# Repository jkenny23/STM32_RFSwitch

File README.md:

# STM32_RFSwitch
12V RF switch/DC relay controller (7 channels) and open-drain button press emulator (6 channels) with switchable USB2.0/USB3.0 ports with independent voltage/current monitoring. Includes 2 thermistor channels, and 2 spare ADC, 2 spare GPIO, and 1 spare GPI channel.

Zip file contains Gerbers ready for fab (2-up panel), and xlsx files contain BOM/component placement list also needed for fab by JLCPCB SMT service. Estimated cost is $61.77 for PCBA including DHL shipping (10 boards total, 5 panels), plus $18.12 for additional components from LCSC (through hole headers, inductor, USB connectors), and $16.86 for the STM32 "blue pill" microcontroller boards, for a total of $96.75 ($9.68 per board).

Usage:

RF Switch: r[1-7]

USB2.0 Power Control: l[1-2, 1=off, 2=on]

USB3.0 Power Control:  m[1-2, 1=off, 2=on]

Open Drain Output: o[1-6] l[level: 0 = open, 1 = low, default 0] d[delay, x0.1s, deafult 10 (1s)]

Cal R/W Mode: t[r/w] a[address: 0-999] d[data, unsigned int (0-65535)]

Version: v

Status: s

Soft Reset: z

Help (Prints this menu): ?

# Compatible RF Switches

| RF Switch P/N | RF Switch Mfg. | RF Switch Config | # IOs | CH/CL | Notes                                                             | RF Switch Datasheet                                                                        | Approx. Price         |
|---------------|----------------|------------------|-------|-------|-------------------------------------------------------------------|--------------------------------------------------------------------------------------------|-----------------------|
| 2SE1T11JB     | Ducommun       | SPDT             | 2     | CL    |                                                                   | https://www.ducommun.com/pdf/mwcat/2s.pdf                                                  | $18.75-20             |
| 431-420823    | Dow-Key        | SP3T             | 3     | CH    | Remove pull up resistor (R5/R15/R19/R25/R38/R47/R55) for IOs used | https://www.dowkey.com/wp-content/uploads/2015/06/_plk49_1_431461_Latching_CatalogPage.pdf | ~$36 (similar models) |

# Errata
The +/- input are swapped for the MCP6002 op-amp 2 (USB3.0 current measurement). The traces need to be cut and jumpered per the image below:

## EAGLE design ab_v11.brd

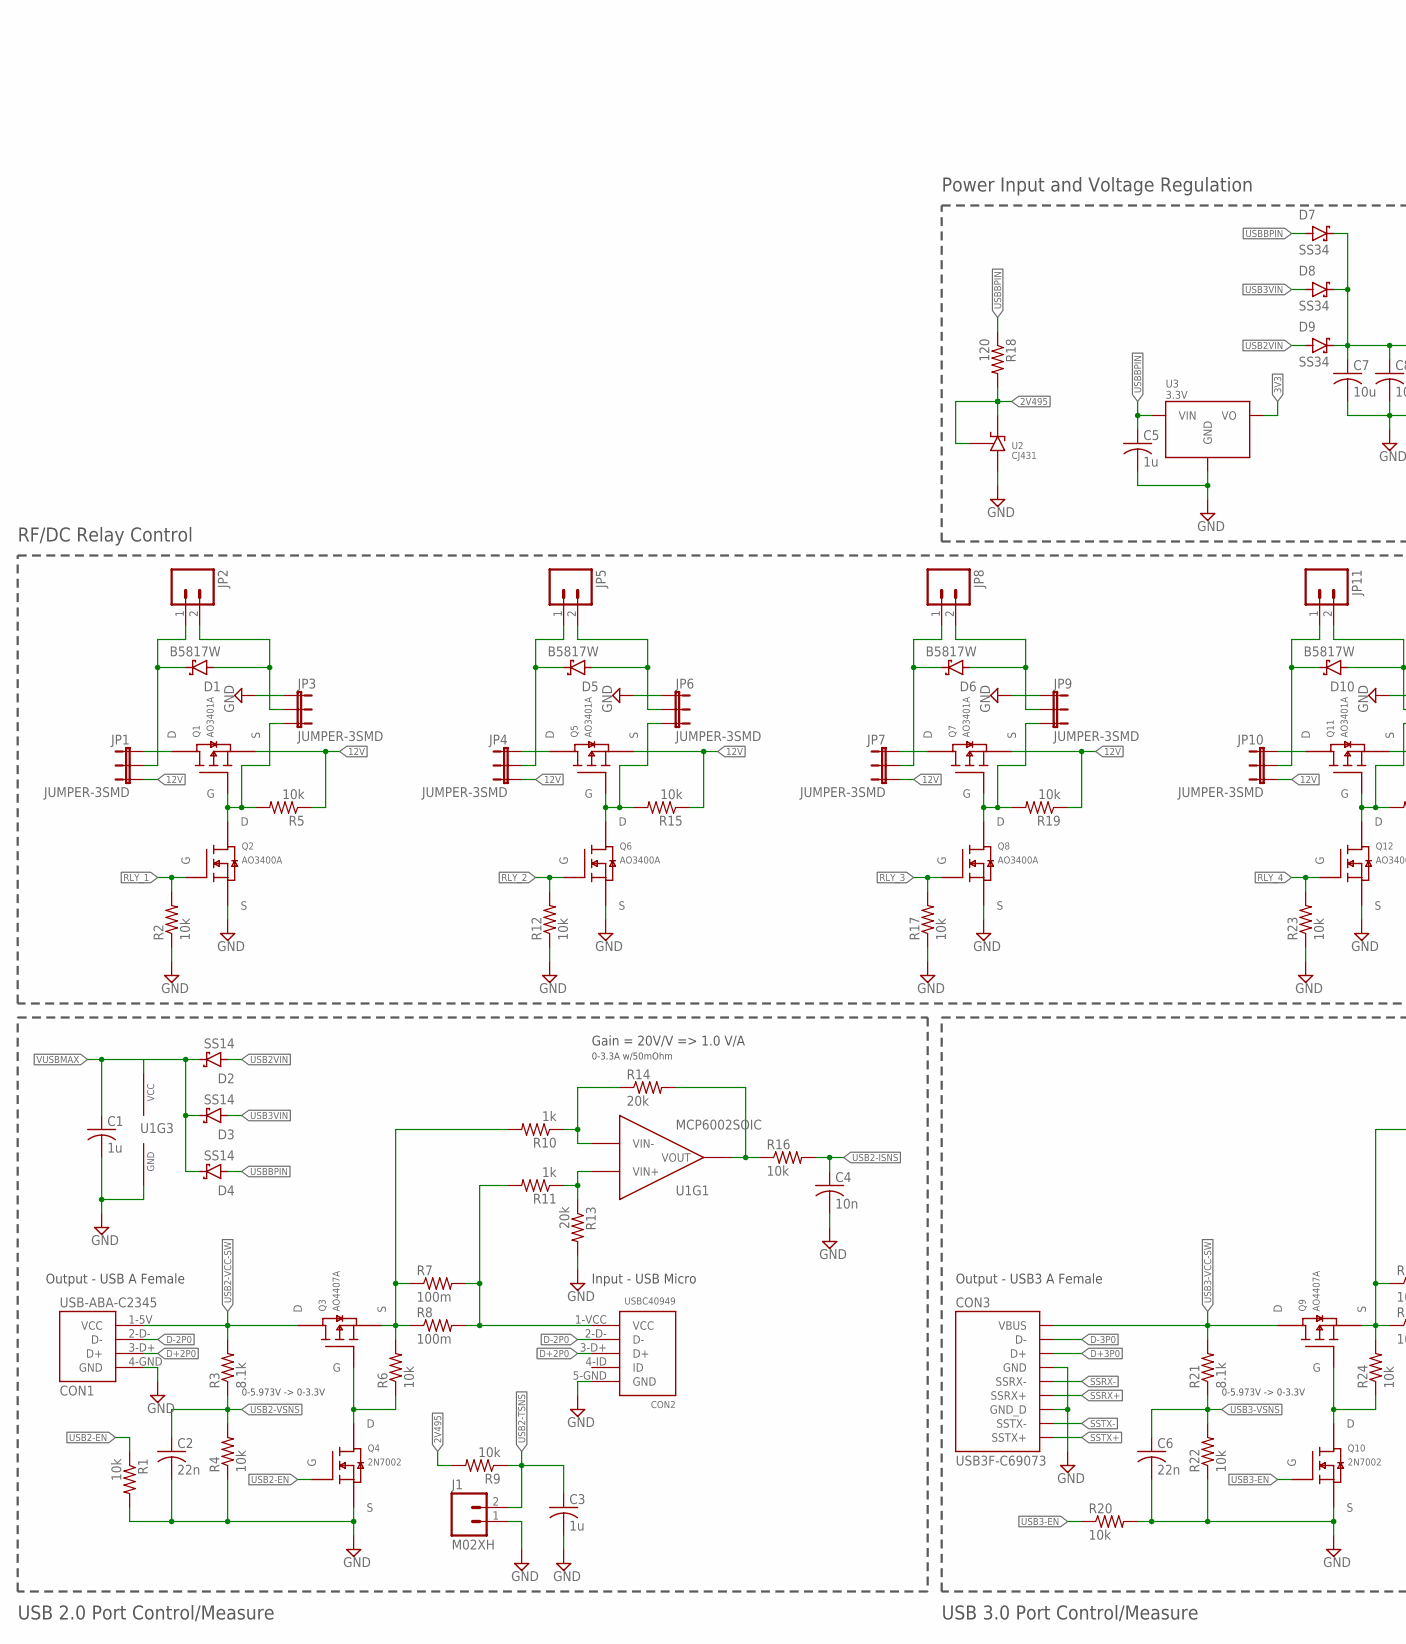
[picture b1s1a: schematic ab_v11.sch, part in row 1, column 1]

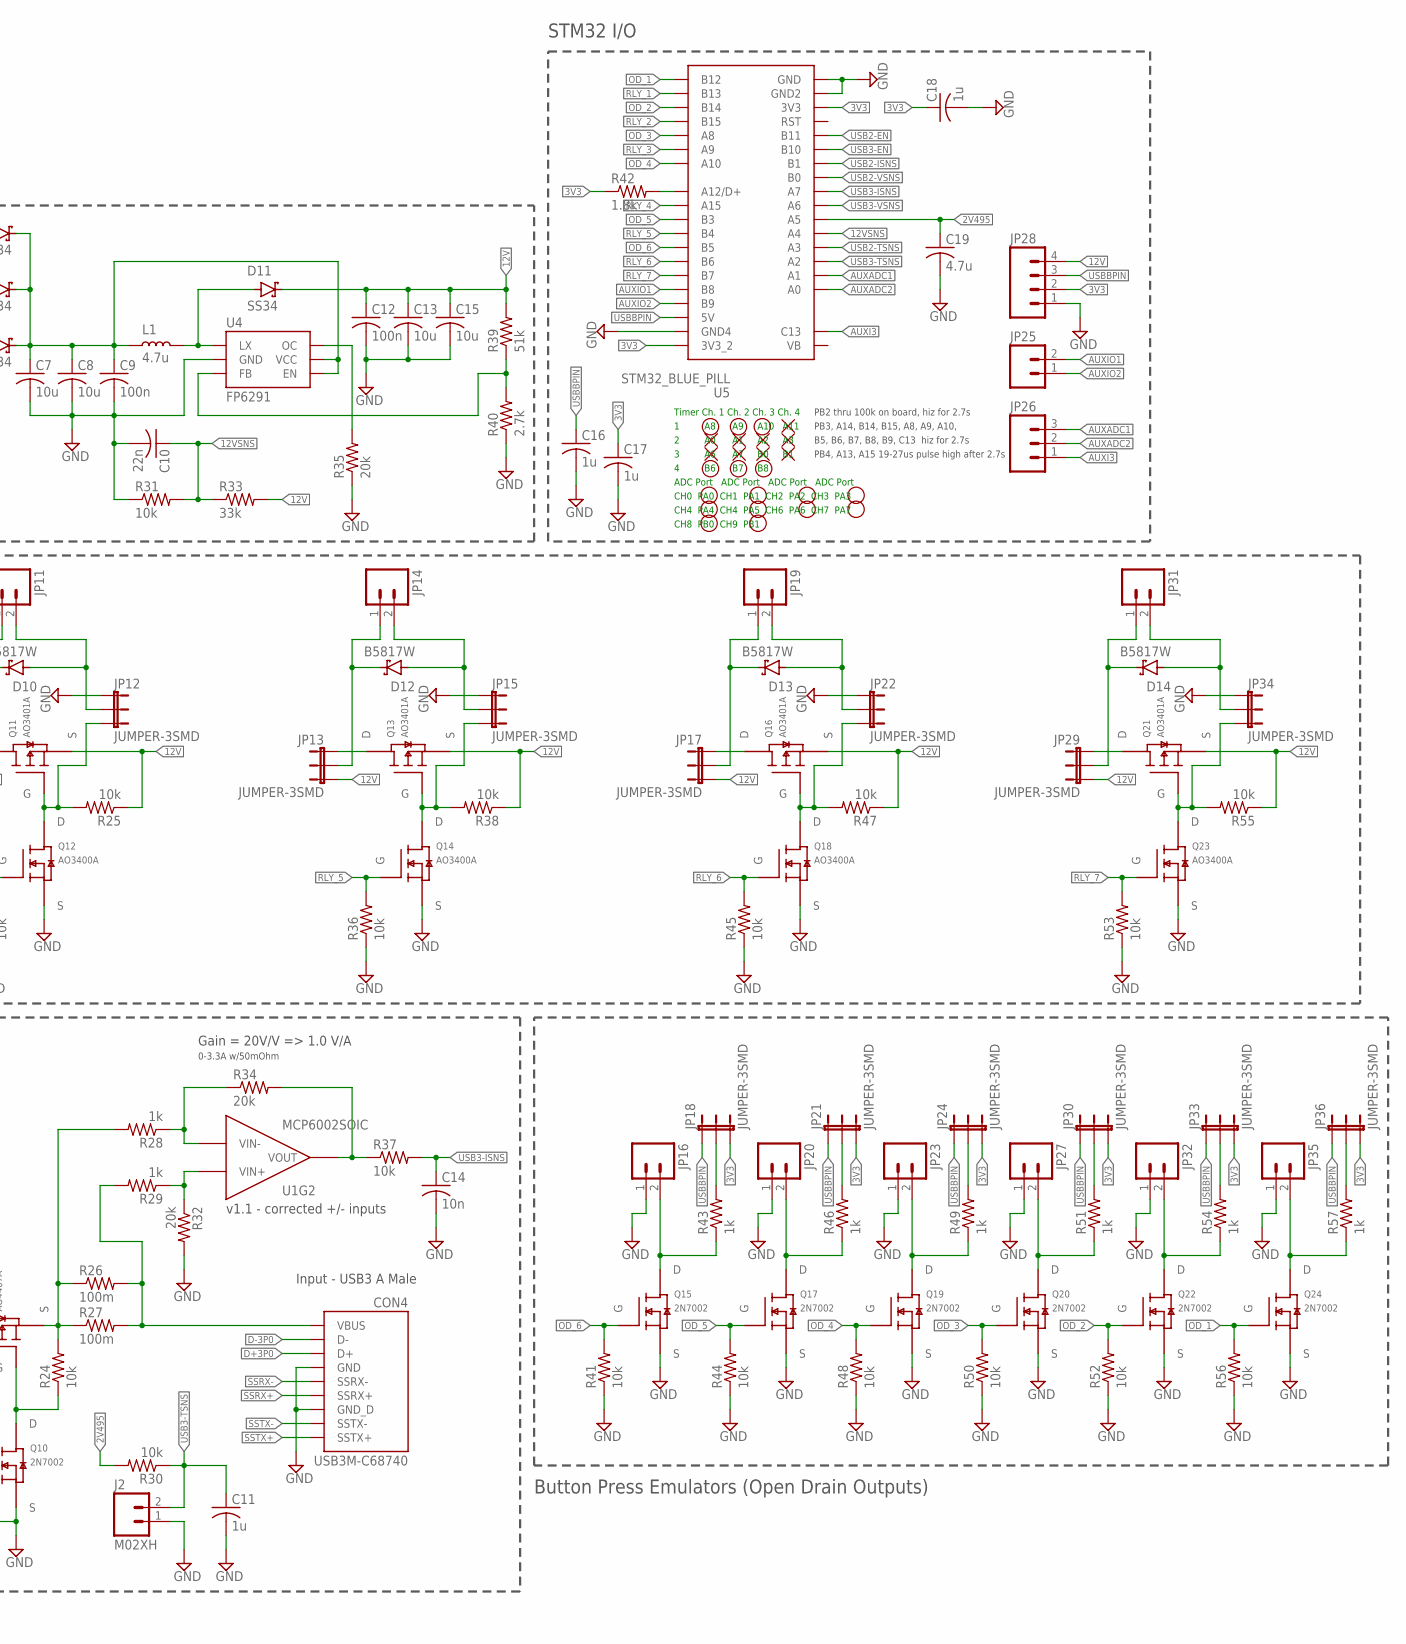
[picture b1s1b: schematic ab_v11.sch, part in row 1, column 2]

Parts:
C1, C3, C5, C11, C16, C17, C18: 1u; C0402
C2, C6, C10: 22n; C0402
C4, C14: 10n; C0402
C7, C8: 10u; C0603
C9, C12: 100n; C0402
C13, C15: 10u; C0805
C19: 4.7u; C0402
CON1: USB-ABA-C2345; USB_A_C2345
CON2: USBC40949; MICRO_USB-B_C40949
CON3: USB3F-C69073; USB3-F-C69073
CON4: USB3M-C68740; USB3-M-C68740
D1, D5, D6, D10, D12, D13, D14: B5817W; SOD123W
D2, D3, D4: SS14; SMA
D7, D8, D9, D11: SS34; SMA
J1, J2: M02XH; B2B-XH-A
JP1, JP3, JP4, JP6, JP7, JP9, JP10, JP12, JP13, JP15, JP17, JP18, JP21, JP22, JP24, JP29, JP30, JP33, JP34, JP36: JUMPER-3SMD; SJ_3
JP2, JP5, JP8, JP11, JP14, JP16, JP19, JP20, JP23, JP25, JP27, JP31, JP32, JP35: M02PTH; 1X02
JP26: M03PTH; 1X03
JP28: M04PTH; 1X04
L1: 4.7u; INDUCTOR_6X6
Q1, Q5, Q7, Q11, Q13, Q16, Q21: AO3401A; SOT23
Q2, Q6, Q8, Q12, Q14, Q18, Q23: AO3400A; SOT23
Q3, Q9: AO4407A; 8-SOIC
Q4, Q10, Q15, Q17, Q19, Q20, Q22, Q24: 2N7002; SOT23
R1, R2, R4, R5, R6, R9, R12, R15, R16, R17, R19, R20, R22, R23, R24, R25, R30, R31, R36, R37, R38, R41, R44, R45, R47, R48, R50, R52, R53, R55, R56: 10k; R0402
R3, R21: 8.1k; R0402
R7, R8, R26, R27: 100m; R1206
R10, R11, R28, R29, R43, R46, R49, R51, R54, R57: 1k; R0402
R13, R14, R32, R34, R35: 20k; R0402
R18: 120; R0402
R33: 33k; R0402
R39: 51k; R0402
R40: 2.7k; R0402
R42: 1.8k; R0402
U1: MCP6002SOIC; 8-SOIC
U2: CJ431; SOT23
U3: 3.3V; SOT-89
U4: FP6291; SOT23-6
U5: STM32_BLUE_PILL; STM32_BLUE_PILL_USABLE

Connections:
2V495: C19.1, R9.2, R18.2, R30.2, U2.1 (K), U2.2 (REF), U5.A5
3V3: C17.1, C18.1, JP18.3, JP21.3, JP24.3, JP28.2, JP30.3, JP33.3, JP36.3, R42.1, U3.1 (VO), U5.3V3, U5.3V3_2
12V: C12.1, C13.1, C15.1, D11.K (CATHODE), JP1.3, JP4.3, JP7.3, JP10.3, JP13.3, JP17.3, JP28.4, JP29.3, Q1.2 (S), Q5.2 (S), Q7.2 (S), Q11.2 (S), Q13.2 (S), Q16.2 (S), Q21.2 (S), R5.1, R15.1, R19.1, R25.1, R33.2, R38.1, R39.2, R47.1, R55.1
12VSNS: C10.1, R31.2, R33.1, U5.A4
AUXADC1: JP26.3, U5.A1
AUXADC2: JP26.2, U5.A0
AUXI3: JP26.1, U5.C13
AUXIO1: JP25.2, U5.B8
AUXIO2: JP25.1, U5.B9
BOOSTVCC: C7.1, C8.1, C9.1, D7.K (CATHODE), D8.K (CATHODE), D9.K (CATHODE), L1.1, U4.4 (EN), U4.5 (VCC)
D+2P0: CON1.3-D+ (D+), CON2.3-D+ (D+)
D+3P0: CON3.3-D+ (D+), CON4.3-D+ (D+)
D-2P0: CON1.2-D- (D-), CON2.2-D- (D-)
D-3P0: CON3.2-D- (D-), CON4.2-D- (D-)
FB: R39.1, R40.2, U4.3 (FB)
GND: C1.2, C2.2, C3.2, C4.2, C5.2, C6.2, C7.2, C8.2, C9.2, C10.2, C11.2, C12.2, C13.2, C14.2, C15.2, C16.2, C17.2, C18.2, C19.2, CON1.4-GND (GND), CON2.5-GND (GND), CON3.4-GND (GND), CON3.7-GND (GND_D), CON4.4-GND (GND), CON4.7-GNDD (GND_D), J1.1, J2.1, JP3.1, JP6.1, JP9.1, JP12.1, JP15.1, JP16.1, JP20.1, JP22.1, JP23.1, JP27.1, JP28.1, JP32.1, JP34.1, JP35.1, Q2.2 (S), Q4.2 (S), Q6.2 (S), Q8.2 (S), Q10.2 (S), Q12.2 (S), Q14.2 (S), Q15.2 (S), Q17.2 (S), Q18.2 (S), Q19.2 (S), Q20.2 (S), Q22.2 (S), Q23.2 (S), Q24.2 (S), R1.2, R2.1, R4.1, R12.1, R13.2, R17.1, R20.2, R22.1, R23.1, R31.1, R32.2, R35.1, R36.1, R40.1, R41.1, R44.1, R45.1, R48.1, R50.1, R52.1, R53.1, R56.1, U1.4 (GND), U2.3 (A), U3.2 (GND), U3.2@1 (GND), U4.2 (GND), U5.GND, U5.GND2, U5.GND4
unnamed: JP16.2, Q15.3 (D), R43.1
unnamed: Q9.4 (G), Q10.3 (D), R24.1
unnamed: R10.1, R14.1, U1.2 (VIN-)
unnamed: R11.1, R13.1, U1.3 (VIN+)
unnamed: JP21.2, R46.2
unnamed: JP18.2, R43.2
unnamed: Q3.4 (G), Q4.3 (D), R6.1
unnamed: JP20.2, Q17.3 (D), R46.1
unnamed: JP24.2, R49.2
unnamed: JP23.2, Q19.3 (D), R49.1
unnamed: JP30.2, R51.2
unnamed: JP27.2, Q20.3 (D), R51.1
unnamed: JP33.2, R54.2
unnamed: JP32.2, Q22.3 (D), R54.1
unnamed: JP36.2, R57.2
unnamed: R28.1, R34.1, U1.6 (VIN-)
unnamed: R29.1, R32.1, U1.5 (VIN+)
unnamed: JP35.2, Q24.3 (D), R57.1
unnamed: JP6.3, Q5.1 (G), Q6.3 (D), R15.2
unnamed: R42.2, U5.A12 (A12/D+)
OC: R35.2, U4.6 (OC)
OD_1: Q24.1 (G), R56.2, U5.B12
OD_2: Q22.1 (G), R52.2, U5.B14
OD_3: Q20.1 (G), R50.2, U5.A8
OD_4: Q19.1 (G), R48.2, U5.A10
OD_5: Q17.1 (G), R44.2, U5.B3
OD_6: Q15.1 (G), R41.2, U5.B5
RLY1-SW: D1.K (CATHODE), JP1.2, JP2.1
RLY1-SW1: D5.K (CATHODE), JP4.2, JP5.1
RLY1-SW2: D6.K (CATHODE), JP7.2, JP8.1
RLY1-SW3: D10.K (CATHODE), JP10.2, JP11.1
RLY1-SW4: D12.K (CATHODE), JP13.2, JP14.1
RLY1-SW5: D13.K (CATHODE), JP17.2, JP19.1
RLY1-SW6: D14.K (CATHODE), JP29.2, JP31.1
RLY1D: JP1.1, Q1.3 (D)
RLY1D1: JP4.1, Q5.3 (D)
RLY1D2: JP7.1, Q7.3 (D)
RLY1D3: JP10.1, Q11.3 (D)
RLY1D4: JP13.1, Q13.3 (D)
RLY1D5: JP17.1, Q16.3 (D)
RLY1D6: JP29.1, Q21.3 (D)
RLY1DG: JP3.3, Q1.1 (G), Q2.3 (D), R5.2
RLY1DG2: JP9.3, Q7.1 (G), Q8.3 (D), R19.2
RLY1DG3: JP12.3, Q11.1 (G), Q12.3 (D), R25.2
RLY1DG4: JP15.3, Q13.1 (G), Q14.3 (D), R38.2
RLY1DG5: JP22.3, Q16.1 (G), Q18.3 (D), R47.2
RLY1DG6: JP34.3, Q21.1 (G), Q23.3 (D), R55.2
RLY1SPLY: D1.A (ANODE), JP2.2, JP3.2
RLY1SPLY1: D5.A (ANODE), JP5.2, JP6.2
RLY1SPLY2: D6.A (ANODE), JP8.2, JP9.2
RLY1SPLY3: D10.A (ANODE), JP11.2, JP12.2
RLY1SPLY4: D12.A (ANODE), JP14.2, JP15.2
RLY1SPLY5: D13.A (ANODE), JP19.2, JP22.2
RLY1SPLY6: D14.A (ANODE), JP31.2, JP34.2
RLY_1: Q2.1 (G), R2.2, U5.B13
RLY_2: Q6.1 (G), R12.2, U5.B15
RLY_3: Q8.1 (G), R17.2, U5.A9
RLY_4: Q12.1 (G), R23.2, U5.A15
RLY_5: Q14.1 (G), R36.2, U5.B4
RLY_6: Q18.1 (G), R45.2, U5.B6
RLY_7: Q23.1 (G), R53.2, U5.B7
SSRX+: CON3.6-SSRX+ (SSRX+), CON4.6-SSRX+ (SSRX+)
SSRX-: CON3.5-SSRX- (SSRX-), CON4.5-SSRX- (SSRX-)
SSTX+: CON3.9-SSTX+ (SSTX+), CON4.9-SSTX+ (SSTX+)
SSTX-: CON3.8-SSTX- (SSTX-), CON4.8-SSTX- (SSTX-)
SW: D11.A (ANODE), L1.2, U4.1 (LX)
USB2-EN: Q4.1 (G), R1.1, U5.B11
USB2-ISNS: C4.1, R16.2, U5.B1
USB2-ISNS-R: R14.2, R16.1, U1.1 (VOUT)
USB2-TSNS: C3.1, J1.2, R9.1, U5.A3
USB2-VCC-SW: CON1.1-5V (VCC), Q3.5 (D), Q3.6 (D), Q3.7 (D), Q3.8 (D), R3.2
USB2-VSNS: C2.1, R3.1, R4.2, U5.B0
USB2VIN: CON2.1-VCC (VCC), D2.A (ANODE), D9.A (ANODE), R7.2, R8.2, R11.2
USB3-EN: Q10.1 (G), R20.1, U5.B10
USB3-ISNS: C14.1, R37.2, U5.A7
USB3-ISNS-R: R34.2, R37.1, U1.7 (VOUT)
USB3-TSNS: C11.1, J2.2, R30.1, U5.A2
USB3-VCC-SW: CON3.1-VBUS (VBUS), Q9.5 (D), Q9.6 (D), Q9.7 (D), Q9.8 (D), R21.2
USB3-VSNS: C6.1, R21.1, R22.2, U5.A6
USB3OUTVCC: Q9.1 (S), Q9.2 (S), Q9.3 (S), R24.2, R26.1, R27.1, R28.2
USB3VIN: CON4.1-VBUS (VBUS), D3.A (ANODE), D8.A (ANODE), R26.2, R27.2, R29.2
USBBPIN: C5.1, C16.1, D4.A (ANODE), D7.A (ANODE), JP18.1, JP21.1, JP24.1, JP28.3, JP30.1, JP33.1, JP36.1, R18.1, U3.3 (VIN), U5.5V
USBOUTVCC: Q3.1 (S), Q3.2 (S), Q3.3 (S), R6.2, R7.1, R8.1, R10.2
VUSBMAX: C1.1, D2.K (CATHODE), D3.K (CATHODE), D4.K (CATHODE), U1.8 (VCC)

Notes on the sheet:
Gain = 20V/V => 1.0 V/A
0-3.3A w/50mOhm
0-5.973V -> 0-3.3V
STM32 I/O
Timer Ch. 1 Ch. 2 Ch. 3 Ch. 4
1 A8 A9 A10 A11
2 A0 A1 A2 A3
3 A6 A7 B0 B1
4 B6 B7 B8
ADC Port ADC Port ADC Port ADC Port
CH0 PA0 CH1 PA1 CH2 PA2 CH3 PA3
CH4 PA4 CH4 PA5 CH6 PA6 CH7 PA7
CH8 PB0 CH9 PB1
PB2 thru 100k on board, hiz for 2.7s
PB3, A14, B14, B15, A8, A9, A10,
PB4, A13, A15 19-27us pulse high after 2.7s
B5, B6, B7, B8, B9, C13 hiz for 2.7s
USB 2.0 Port Control/Measure
Power Input and Voltage Regulation
Button Press Emulators (Open Drain Outputs)
Input - USB Micro
Output - USB A Female
USB 3.0 Port Control/Measure
Input - USB3 A Male
Output - USB3 A Female
RF/DC Relay Control
v1.1 - corrected +/- inputs

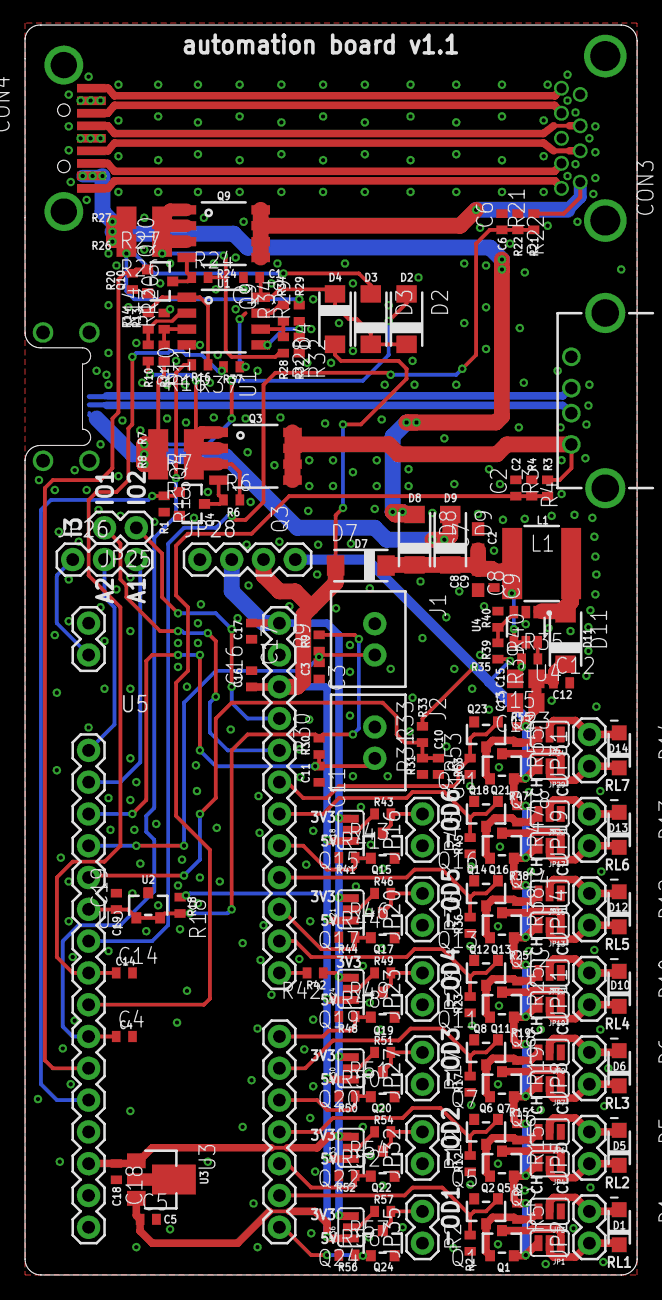
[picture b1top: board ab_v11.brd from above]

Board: 2 copper layers, 48.9 x 99.9 mm, 162 parts (1 on the bottom side), 100 nets.

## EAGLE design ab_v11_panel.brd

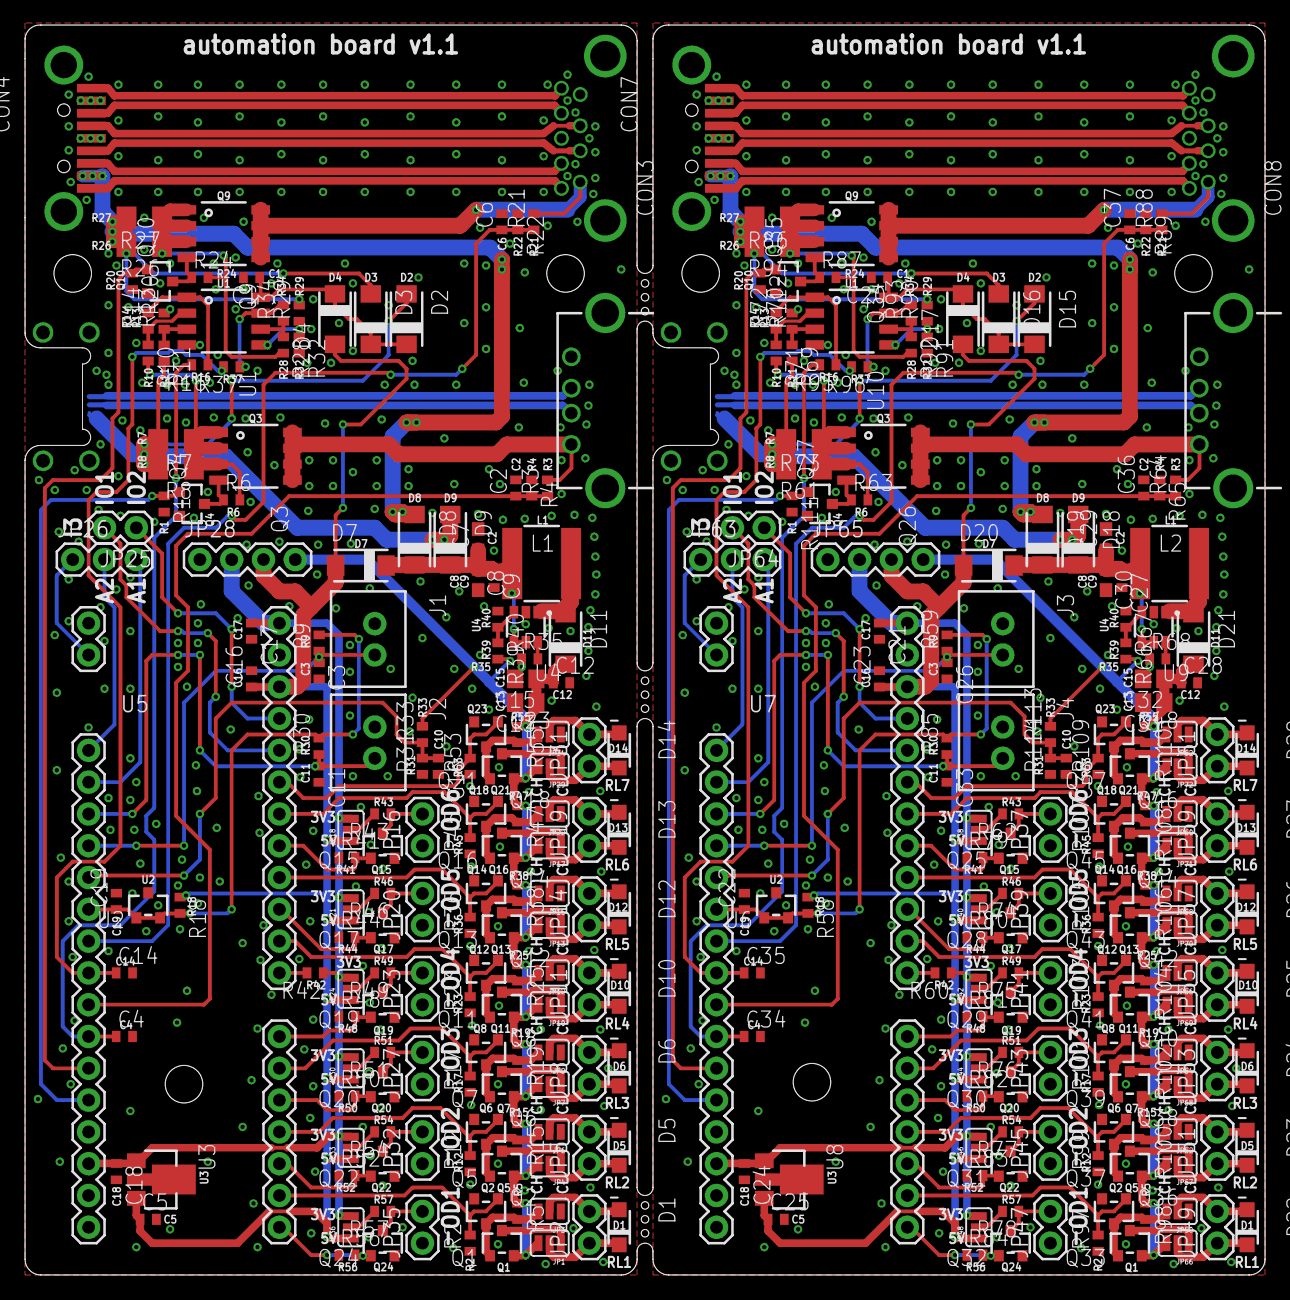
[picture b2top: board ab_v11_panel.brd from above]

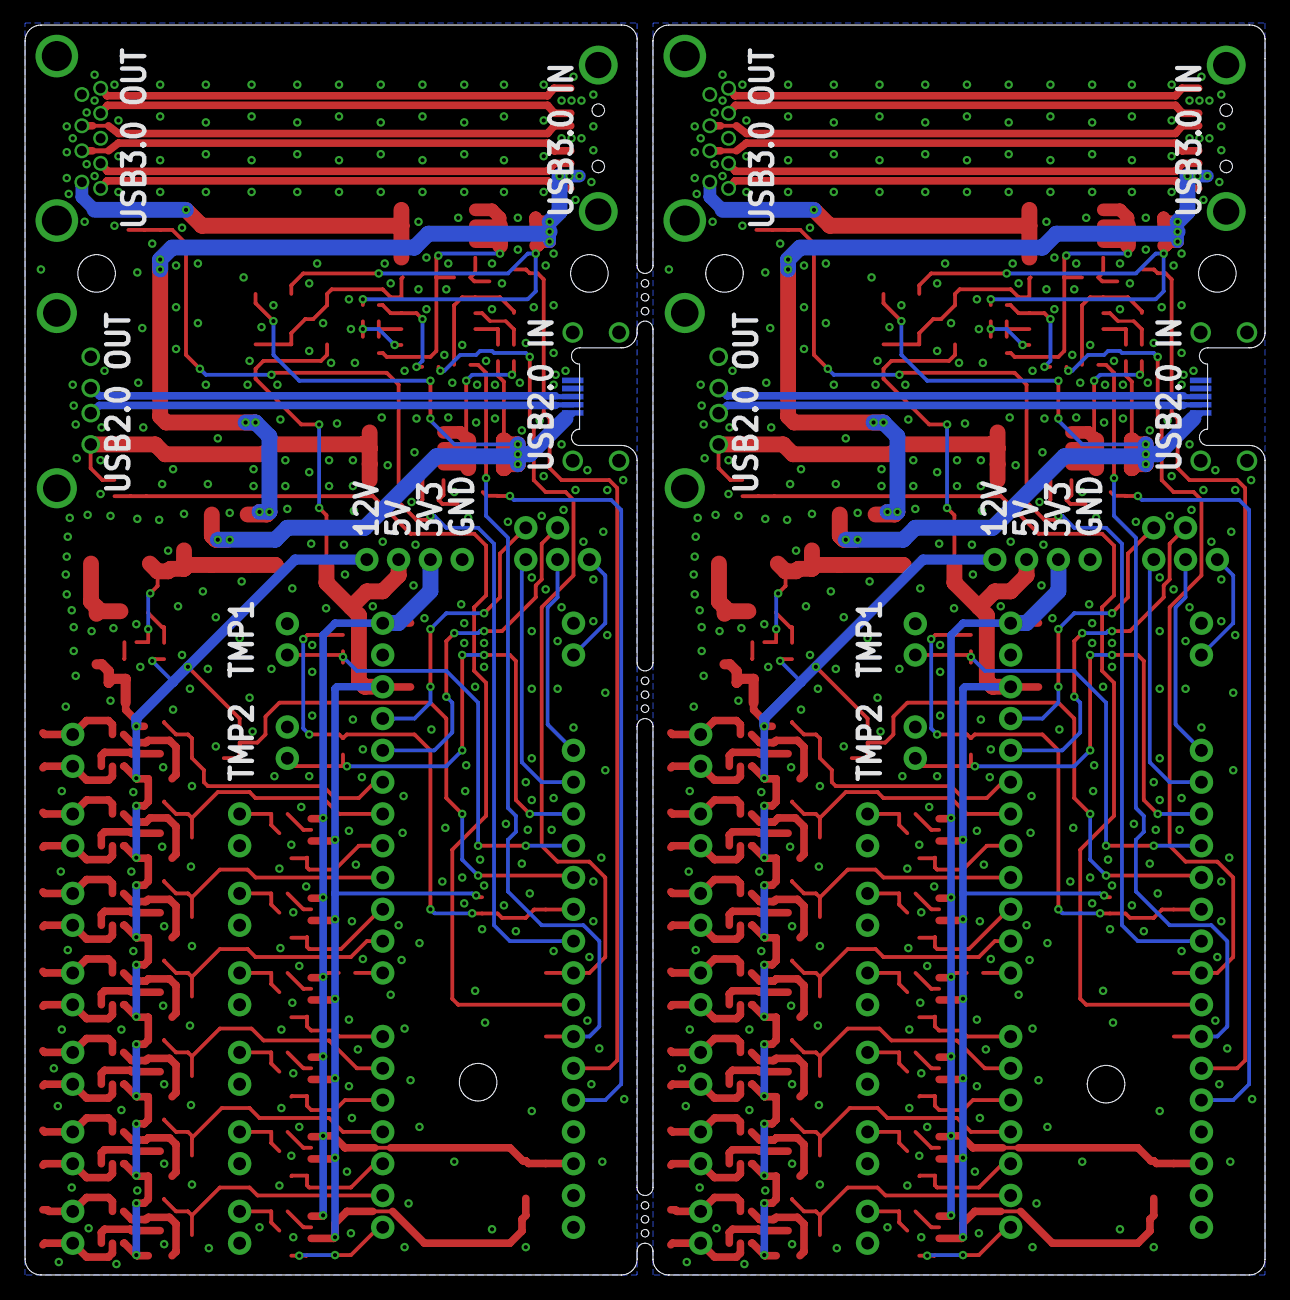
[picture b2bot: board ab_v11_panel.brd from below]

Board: 2 copper layers, 99.1 x 99.9 mm, 324 parts (2 on the bottom side), 200 nets.

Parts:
C1, C3, C5, C11, C16, C17, C18, C20, C21, C23, C24, C25, C26, C33: 1u; C0402
C2, C6, C10, C36, C37, C38: 22n; C0402
C4, C14, C34, C35: 10n; C0402
C7, C8, C29, C30: 10u; C0603
C9, C12, C27, C28: 100n; C0402
C13, C15, C31, C32: 10u; C0805
C19, C22: 4.7u; C0402
CON1, CON6: USB-ABA-C2345; USB_A_C2345
CON2, CON5: USBC40949; MICRO_USB-B_C40949
CON3, CON8: USB3F-C69073; USB3-F-C69073
CON4, CON7: USB3M-C68740; USB3-M-C68740
D1, D5, D6, D10, D12, D13, D14, D22, D23, D24, D25, D26, D27, D28: B5817W; SOD123W
D2, D3, D4, D15, D16, D17: SS14; SMA
D7, D8, D9, D11, D18, D19, D20, D21: SS34; SMA
J1, J2, J3, J4: M02XH; B2B-XH-A
JP1, JP3, JP4, JP6, JP7, JP9, JP10, JP12, JP13, JP15, JP17, JP18, JP21, JP22, JP24, JP29, JP30, JP33, JP34, JP36, JP38, JP40, JP42, JP44, JP46, JP48, JP50, JP52, JP54, JP56, JP58, JP60, JP62, JP66, JP67, JP68, JP69, JP70, JP71, JP72: JUMPER-3SMD; SJ_3
JP2, JP5, JP8, JP11, JP14, JP16, JP19, JP20, JP23, JP25, JP27, JP31, JP32, JP35, JP37, JP39, JP41, JP43, JP45, JP47, JP49, JP51, JP53, JP55, JP57, JP59, JP61, JP64: 1X02
JP26, JP63: 1X03
JP28, JP65: 1X04
L1, L2: 4.7u; INDUCTOR_6X6
Q1, Q5, Q7, Q11, Q13, Q16, Q21, Q33, Q37, Q39, Q41, Q43, Q45, Q47: AO3401A; SOT23
Q2, Q6, Q8, Q12, Q14, Q18, Q23, Q36, Q38, Q40, Q42, Q44, Q46, Q48: AO3400A; SOT23
Q3, Q9, Q26, Q34: AO4407A; 8-SOIC
Q4, Q10, Q15, Q17, Q19, Q20, Q22, Q24, Q25, Q27, Q28, Q29, Q30, Q31, Q32, Q35: 2N7002; SOT23
R1, R2, R4, R5, R6, R9, R12, R15, R16, R17, R19, R20, R22, R23, R24, R25, R30, R31, R36, R37, R38, R41, R44, R45, R47, R48, R50, R52, R53, R55, R56, R59, R63, R65, R79, R80, R81, R82, R83, R84, R85, R87, R89, R95, R96, R97, R98, R99, R100, R101, R102, R103, R104, R105, R106, R107, R108, R109, R110, R111, R112, R114: 10k; R0402
R3, R21, R64, R88: 8.1k; R0402
R7, R8, R26, R27, R61, R73, R86, R94: 100m; R1206
R10, R11, R28, R29, R43, R46, R49, R51, R54, R57, R62, R69, R71, R74, R75, R76, R77, R78, R90, R92: 1k; R0402
R13, R14, R32, R34, R35, R68, R70, R72, R91, R93: 20k; R0402
R18, R58: 120; R0402
R33, R113: 33k; R0402
R39, R66: 51k; R0402
R40, R67: 2.7k; R0402
R42, R60: 1.8k; R0402
U1, U10: MCP6002SOIC; 8-SOIC
U2, U6: CJ431; SOT23
U3, U8: 3.3V; SOT-89
U4, U9: FP6291; SOT23-6
U5, U7: STM32_BLUE_PILL; STM32_BLUE_PILL_USABLE

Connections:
2V1: C22.1, R58.2, R59.2, R85.2, U6.1, U6.2, U7.A5
2V495: C19.1, R9.2, R18.2, R30.2, U2.1, U2.2, U5.A5
3V1: C21.1, C24.1, JP38.3, JP40.3, JP42.3, JP44.3, JP46.3, JP48.3, JP65.2, R60.1, U7.3V3, U7.3V3_2, U8.1
3V3: C17.1, C18.1, JP18.3, JP21.3, JP24.3, JP28.2, JP30.3, JP33.3, JP36.3, R42.1, U3.1, U5.3V3, U5.3V3_2
12V: C12.1, C13.1, C15.1, D11.K, JP1.3, JP4.3, JP7.3, JP10.3, JP13.3, JP17.3, JP28.4, JP29.3, Q1.2, Q5.2, Q7.2, Q11.2, Q13.2, Q16.2, Q21.2, R5.1, R15.1, R19.1, R25.1, R33.2, R38.1, R39.2, R47.1, R55.1
12V1: C28.1, C31.1, C32.1, D21.K, JP65.4, JP66.3, JP67.3, JP68.3, JP69.3, JP70.3, JP71.3, JP72.3, Q33.2, Q37.2, Q39.2, Q41.2, Q43.2, Q45.2, Q47.2, R66.2, R98.1, R100.1, R102.1, R104.1, R106.1, R108.1, R110.1, R113.2
12VSNS: C10.1, R31.2, R33.1, U5.A4
12VSNS1: C38.1, R113.1, R114.2, U7.A4
AUXADC1: JP26.3, U5.A1
AUXADC2: JP26.2, U5.A0
AUXADC3: JP63.3, U7.A1
AUXADC4: JP63.2, U7.A0
AUXI1: JP63.1, U7.C13
AUXI3: JP26.1, U5.C13
AUXIO1: JP25.2, U5.B8
AUXIO2: JP25.1, U5.B9
AUXIO3: JP64.1, U7.B9
AUXIO4: JP64.2, U7.B8
BOOSTVCC: C7.1, C8.1, C9.1, D7.K, D8.K, D9.K, L1.1, U4.4, U4.5
BOOSTVCC1: C27.1, C29.1, C30.1, D18.K, D19.K, D20.K, L2.1, U9.4, U9.5
D+2P0: CON1.3-D+, CON2.3-D+
D+2P1: CON5.3-D+, CON6.3-D+
D+3P0: CON3.3-D+, CON4.3-D+
D+3P1: CON7.3-D+, CON8.3-D+
D-2P0: CON1.2-D-, CON2.2-D-
D-2P1: CON5.2-D-, CON6.2-D-
D-3P0: CON3.2-D-, CON4.2-D-
D-3P1: CON7.2-D-, CON8.2-D-
FB: R39.1, R40.2, U4.3
FB1: R66.1, R67.2, U9.3
GND: C1.2, C2.2, C3.2, C4.2, C5.2, C6.2, C7.2, C8.2, C9.2, C10.2, C11.2, C12.2, C13.2, C14.2, C15.2, C16.2, C17.2, C18.2, C19.2, CON1.4-GND, CON2.5-GND, CON3.4-GND, CON3.7-GND, CON4.4-GND, CON4.7-GNDD, J1.1, J2.1, JP3.1, JP6.1, JP9.1, JP12.1, JP15.1, JP16.1, JP20.1, JP22.1, JP23.1, JP27.1, JP28.1, JP32.1, JP34.1, JP35.1, Q2.2, Q4.2, Q6.2, Q8.2, Q10.2, Q12.2, Q14.2, Q15.2, Q17.2, Q18.2, Q19.2, Q20.2, Q22.2, Q23.2, Q24.2, R1.2, R2.1, R4.1, R12.1, R13.2, R17.1, R20.2, R22.1, R23.1, R31.1, R32.2, R35.1, R36.1, R40.1, R41.1, R44.1, R45.1, R48.1, R50.1, R52.1, R53.1, R56.1, U1.4, U2.3, U3.2, U3.2@1, U4.2, U5.GND, U5.GND2, U5.GND4
GND1: C20.2, C21.2, C22.2, C23.2, C24.2, C25.2, C26.2, C27.2, C28.2, C29.2, C30.2, C31.2, C32.2, C33.2, C34.2, C35.2, C36.2, C37.2, C38.2, CON5.5-GND, CON6.4-GND, CON7.4-GND, CON7.7-GNDD, CON8.4-GND, CON8.7-GND, J3.1, J4.1, JP37.1, JP39.1, JP41.1, JP43.1, JP45.1, JP47.1, JP50.1, JP52.1, JP54.1, JP56.1, JP58.1, JP60.1, JP62.1, JP65.1, Q25.2, Q27.2, Q28.2, Q29.2, Q30.2, Q31.2, Q32.2, Q35.2, Q36.2, Q38.2, Q40.2, Q42.2, Q44.2, Q46.2, Q48.2, R65.1, R67.1, R68.1, R70.2, R79.1, R80.1, R81.1, R82.1, R83.1, R84.1, R89.1, R91.2, R97.1, R99.1, R101.1, R103.1, R105.1, R107.1, R109.1, R111.2, R112.2, R114.1, U6.3, U7.GND, U7.GND2, U7.GND4, U8.2, U8.2@1, U9.2, U10.4
unnamed: JP16.2, Q15.3, R43.1
unnamed: Q9.4, Q10.3, R24.1
unnamed: R10.1, R14.1, U1.2
unnamed: R11.1, R13.1, U1.3
unnamed: JP21.2, R46.2
unnamed: JP18.2, R43.2
unnamed: Q3.4, Q4.3, R6.1
unnamed: JP20.2, Q17.3, R46.1
unnamed: JP24.2, R49.2
unnamed: JP23.2, Q19.3, R49.1
unnamed: JP30.2, R51.2
unnamed: JP27.2, Q20.3, R51.1
unnamed: JP33.2, R54.2
unnamed: JP32.2, Q22.3, R54.1
unnamed: JP36.2, R57.2
unnamed: R28.1, R34.1, U1.6
unnamed: R29.1, R32.1, U1.5
unnamed: JP35.2, Q24.3, R57.1
unnamed: R60.2, U7.A12
unnamed: JP6.3, Q5.1, Q6.3, R15.2
unnamed: JP38.2, R62.2
unnamed: Q26.4, Q27.3, R63.1
unnamed: R71.1, R72.1, U10.2
unnamed: R69.1, R70.1, U10.3
unnamed: JP37.2, Q25.3, R62.1
unnamed: R42.2, U5.A12
unnamed: JP40.2, R74.2
unnamed: JP39.2, Q28.3, R74.1
unnamed: JP42.2, R75.2
unnamed: JP41.2, Q29.3, R75.1
unnamed: JP44.2, R76.2
unnamed: JP43.2, Q30.3, R76.1
unnamed: JP46.2, R77.2
unnamed: JP45.2, Q31.3, R77.1
unnamed: JP48.2, R78.2
unnamed: JP47.2, Q32.3, R78.1
unnamed: Q34.4, Q35.3, R87.1
unnamed: R92.1, R93.1, U10.6
unnamed: R90.1, R91.1, U10.5
unnamed: JP52.3, Q37.1, Q38.3, R100.2
OC: R35.2, U4.6
OC1: R68.2, U9.6
OD_1: Q24.1, R56.2, U5.B12
OD_2: Q22.1, R52.2, U5.B14
OD_3: Q20.1, R50.2, U5.A8
OD_4: Q19.1, R48.2, U5.A10
OD_5: Q17.1, R44.2, U5.B3
OD_6: Q15.1, R41.2, U5.B5
OD_7: Q32.1, R84.2, U7.B12
OD_8: Q31.1, R83.2, U7.B14
OD_9: Q30.1, R82.2, U7.A8
OD_10: Q29.1, R81.2, U7.A10
OD_11: Q28.1, R80.2, U7.B3
OD_12: Q25.1, R79.2, U7.B5
RLY1-SW: D1.K, JP1.2, JP2.1
RLY1-SW1: D5.K, JP4.2, JP5.1
RLY1-SW2: D6.K, JP7.2, JP8.1
RLY1-SW3: D10.K, JP10.2, JP11.1
RLY1-SW4: D12.K, JP13.2, JP14.1
RLY1-SW5: D13.K, JP17.2, JP19.1
RLY1-SW6: D14.K, JP29.2, JP31.1
RLY1-SW7: D22.K, JP49.1, JP66.2
RLY1-SW8: D23.K, JP51.1, JP67.2
RLY1-SW9: D24.K, JP53.1, JP68.2
RLY1-SW10: D25.K, JP55.1, JP69.2
RLY1-SW11: D26.K, JP57.1, JP70.2
RLY1-SW12: D27.K, JP59.1, JP71.2
RLY1-SW13: D28.K, JP61.1, JP72.2
RLY1D: JP1.1, Q1.3
RLY1D1: JP4.1, Q5.3
RLY1D2: JP7.1, Q7.3
RLY1D3: JP10.1, Q11.3
RLY1D4: JP13.1, Q13.3
RLY1D5: JP17.1, Q16.3
RLY1D6: JP29.1, Q21.3
RLY1D7: JP66.1, Q33.3
RLY1D8: JP67.1, Q37.3
RLY1D9: JP68.1, Q39.3
RLY1D10: JP69.1, Q41.3
RLY1D11: JP70.1, Q43.3
RLY1D12: JP71.1, Q45.3
RLY1D13: JP72.1, Q47.3
RLY1DG: JP3.3, Q1.1, Q2.3, R5.2
RLY1DG1: JP50.3, Q33.1, Q36.3, R98.2
RLY1DG2: JP9.3, Q7.1, Q8.3, R19.2
RLY1DG3: JP12.3, Q11.1, Q12.3, R25.2
RLY1DG4: JP15.3, Q13.1, Q14.3, R38.2
RLY1DG5: JP22.3, Q16.1, Q18.3, R47.2
RLY1DG6: JP34.3, Q21.1, Q23.3, R55.2
RLY1DG7: JP54.3, Q39.1, Q40.3, R102.2
RLY1DG8: JP56.3, Q41.1, Q42.3, R104.2
RLY1DG9: JP58.3, Q43.1, Q44.3, R106.2
RLY1DG10: JP60.3, Q45.1, Q46.3, R108.2
RLY1DG11: JP62.3, Q47.1, Q48.3, R110.2
RLY1SPLY: D1.A, JP2.2, JP3.2
RLY1SPLY1: D5.A, JP5.2, JP6.2
RLY1SPLY2: D6.A, JP8.2, JP9.2
RLY1SPLY3: D10.A, JP11.2, JP12.2
RLY1SPLY4: D12.A, JP14.2, JP15.2
RLY1SPLY5: D13.A, JP19.2, JP22.2
RLY1SPLY6: D14.A, JP31.2, JP34.2
RLY1SPLY7: D22.A, JP49.2, JP50.2
RLY1SPLY8: D23.A, JP51.2, JP52.2
RLY1SPLY9: D24.A, JP53.2, JP54.2
RLY1SPLY10: D25.A, JP55.2, JP56.2
RLY1SPLY11: D26.A, JP57.2, JP58.2
RLY1SPLY12: D27.A, JP59.2, JP60.2
RLY1SPLY13: D28.A, JP61.2, JP62.2
RLY_1: Q2.1, R2.2, U5.B13
RLY_2: Q6.1, R12.2, U5.B15
RLY_3: Q8.1, R17.2, U5.A9
RLY_4: Q12.1, R23.2, U5.A15
RLY_5: Q14.1, R36.2, U5.B4
RLY_6: Q18.1, R45.2, U5.B6
RLY_7: Q23.1, R53.2, U5.B7
RLY_8: Q36.1, R97.2, U7.B13
RLY_9: Q38.1, R99.2, U7.B15
RLY_10: Q40.1, R101.2, U7.A9
RLY_11: Q42.1, R103.2, U7.A15
RLY_12: Q44.1, R105.2, U7.B4
RLY_13: Q46.1, R107.2, U7.B6
RLY_14: Q48.1, R109.2, U7.B7
SSRX+: CON3.6-SSRX+, CON4.6-SSRX+
SSRX+1: CON7.6-SSRX+, CON8.6-SSRX+
SSRX-: CON3.5-SSRX-, CON4.5-SSRX-
SSRX-1: CON7.5-SSRX-, CON8.5-SSRX-
SSTX+: CON3.9-SSTX+, CON4.9-SSTX+
SSTX+1: CON7.9-SSTX+, CON8.9-SSTX+
SSTX-: CON3.8-SSTX-, CON4.8-SSTX-
SSTX-1: CON7.8-SSTX-, CON8.8-SSTX-
SW: D11.A, L1.2, U4.1
SW1: D21.A, L2.2, U9.1
USB2-EN: Q4.1, R1.1, U5.B11
USB2-EN1: Q27.1, R111.1, U7.B11
USB2-ISNS: C4.1, R16.2, U5.B1
USB2-ISNS1: C34.1, R95.2, U7.B1
USB2-ISNS-R: R14.2, R16.1, U1.1
USB2-ISNS-R1: R72.2, R95.1, U10.1
USB2-TSNS: C3.1, J1.2, R9.1, U5.A3
USB2-TSNS1: C26.1, J3.2, R59.1, U7.A3
USB2-VCC-SW: CON1.1-5V, Q3.5, Q3.6, Q3.7, Q3.8, R3.2
USB2-VCC-SW1: CON6.1-5V, Q26.5, Q26.6, Q26.7, Q26.8, R64.2
USB2-VSNS: C2.1, R3.1, R4.2, U5.B0
USB2-VSNS1: C36.1, R64.1, R65.2, U7.B0
USB2VIN: CON2.1-VCC, D2.A, D9.A, R7.2, R8.2, R11.2
USB2VIN1: CON5.1-VCC, D15.A, D18.A, R61.2, R69.2, R73.2
USB3-EN: Q10.1, R20.1, U5.B10
USB3-EN1: Q35.1, R112.1, U7.B10
USB3-ISNS: C14.1, R37.2, U5.A7
USB3-ISNS1: C35.1, R96.2, U7.A7
USB3-ISNS-R: R34.2, R37.1, U1.7
USB3-ISNS-R1: R93.2, R96.1, U10.7
USB3-TSNS: C11.1, J2.2, R30.1, U5.A2
USB3-TSNS1: C33.1, J4.2, R85.1, U7.A2
USB3-VCC-SW: CON3.1-VBUS, Q9.5, Q9.6, Q9.7, Q9.8, R21.2
USB3-VCC-SW1: CON8.1-VBUS, Q34.5, Q34.6, Q34.7, Q34.8, R88.2
USB3-VSNS: C6.1, R21.1, R22.2, U5.A6
USB3-VSNS1: C37.1, R88.1, R89.2, U7.A6
USB3OUTVCC: Q9.1, Q9.2, Q9.3, R24.2, R26.1, R27.1, R28.2
USB3OUTVCC1: Q34.1, Q34.2, Q34.3, R86.1, R87.2, R92.2, R94.1
USB3VIN: CON4.1-VBUS, D3.A, D8.A, R26.2, R27.2, R29.2
USB3VIN1: CON7.1-VBUS, D16.A, D19.A, R86.2, R90.2, R94.2
USBBPIN: C5.1, C16.1, D4.A, D7.A, JP18.1, JP21.1, JP24.1, JP28.3, JP30.1, JP33.1, JP36.1, R18.1, U3.3, U5.5V
USBBPIN1: C23.1, C25.1, D17.A, D20.A, JP38.1, JP40.1, JP42.1, JP44.1, JP46.1, JP48.1, JP65.3, R58.1, U7.5V, U8.3
USBOUTVCC: Q3.1, Q3.2, Q3.3, R6.2, R7.1, R8.1, R10.2
USBOUTVCC1: Q26.1, Q26.2, Q26.3, R61.1, R63.2, R71.2, R73.1
VUSBMAX: C1.1, D2.K, D3.K, D4.K, U1.8
VUSBMAX1: C20.1, D15.K, D16.K, D17.K, U10.8

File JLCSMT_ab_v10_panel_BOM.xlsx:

Comment | Designator | Footprint | LCSC Part #（optional）
1.8k | R42, R60 | 0402_R | C4177
1k | R10, R11, R28, R29, R43, R46, R49, R51, R54, R57, R62, R69, R71, R74, R75, R76,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 | 0402_R | C11702
1u | C1, C3, C5, C11, C16, C17, C18, C20, C21, C23, C24, C25, C26, C33 | 0402_C | C52923
2.7k | R40, R67 | 0402_R | C13167
2N7002 | Q4, Q10, Q15, Q17, Q19, Q20, Q22, Q24, Q25, Q27, Q28, Q29, Q30, Q31, Q32, Q35 | SOT-23 | C8545
4.7u | C19, C22 | 0402_C | C23733
8.2k | R3, R21, R64, R88 | 0402_R | C25924
10k | R1, R2, R4, R5, R6, R9, R12, R15, R16, R17, R19, R20, R22, R23, R24, R25, R30, 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 | 0402_R | C25744
10n | C4, C14, C34, C35 | 0402_C | C15195
10u | C7, C8, C29, C30 | 0603_C | C19702
10u | C13, C15, C31, C32 | 0805_C | C15850
20k | R13, R14, R32, R34, R35, R68, R70, R72, R91, R93 | 0402_R | C25765
22n | C2, C6, C10, C36, C37, C38 | 0402_C | C1532
33k | R33, R113 | 0402_R | C25779
51k | R39, R66 | 0402_R | C25794
100m | R7, R8, R26, R27, R61, R73, R86, R94 | 1206_R | C25334
100n | C9, C12, C27, C28 | 0402_C | C1525
120 | R18, R58 | 0402_R | C25079
AO3400A | Q2, Q6, Q8, Q12, Q14, Q18, Q23, Q36, Q38, Q40, Q42, Q44, Q46, Q48 | SOT-23 | C20917
AO3401A | Q1, Q5, Q7, Q11, Q13, Q16, Q21, Q33, Q37, Q39, Q41, Q43, Q45, Q47 | SOT-23 | C15127
AO4407A | Q3, Q9, Q26, Q34 | SOIC-8 | C16072
B5817W | D1, D5, D6, D10, D12, D13, D14, D22, D23, D24, D25, D26, D27, D28 | SOD123 | C8598
CJ431 | U2, U6 | SOT-23 | C3113
FP6291 | U4, U9 | SOT-23-6 | C18701
MCP6002SOIC | U1, U10 | SOIC-8 | C7377
SS14 | D2, D3, D4, D15, D16, D17 | SMA | C2480
SS34 | D7, D8, D9, D11, D18, D19, D20, D21 | SMA | C8678

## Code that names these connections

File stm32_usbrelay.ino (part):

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#ifdef BREADBOARD
  #define RFSW_1 PB9
  #define RFSW_2 PB8
  #define OD_1 PB7
  #define OD_2 PB6
  #define RELAY PB5
#endif
#ifdef HW_1P0
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  #define RFSW_5 PB4
  #define RFSW_6 PB6
  #define RFSW_7 PB7
  #define OD_1 PB12
  #define OD_2 PB14
  #define OD_3 PA8
  #define OD_4 PA10
  #define OD_5 PB3
  #define OD_6 PB5
  #define RELAY PB11 //USB2.0, 1=on, 0=off
  #define RELAY2 PB10 //USB3.0, 1=on, 0=off
  #define USB2ISNS PB1
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  #define V12V PA4
  #define TMP1 PA3
  #define TMP2 PA2
  #define AUXADC1 PA1
  #define AUXADC2 PA2
  #define AUXIO1 PB8
  #define AUXIO2 PB9
  #define AUXI13 PC13
#endif

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  digitalWrite(RFSW_1,LOW);
  pinMode(RFSW_2,OUTPUT);
  digitalWrite(RFSW_2,LOW);
  pinMode(OD_1,OUTPUT);
  digitalWrite(OD_1,LOW);
  pinMode(OD_2,OUTPUT);
  digitalWrite(OD_2,LOW);
  pinMode(RELAY,OUTPUT);
  digitalWrite(RELAY,LOW);
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    #define RFSW_5 PB4
    #define RFSW_6 PB6
    #define RFSW_7 PB7
    #define OD_1 PB12
    #define OD_2 PB14
    #define OD_3 PA8
    #define OD_4 PA10
    #define OD_5 PB3
    #define OD_6 PB5
    #define RELAY PB11 //USB2.0, 1=on, 0=off
    #define RELAY2 PB10 //USB3.0, 1=on, 0=off
    #define USB2ISNS PB1
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    #define V12V PA4
    #define TMP1 PA3
    #define TMP2 PA2
    #define AUXADC1 PA1
    #define AUXADC2 PA2
    #define AUXIO1 PB8
    #define AUXIO2 PB9
    #define AUXI13 PC13*/
  #ifdef HW_1P0
    pinMode(RFSW_3,OUTPUT);
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    digitalWrite(RFSW_6,LOW);
    pinMode(RFSW_7,OUTPUT);
    digitalWrite(RFSW_7,LOW);
    pinMode(OD_3,OUTPUT);
    digitalWrite(OD_3,LOW);
    pinMode(OD_4,OUTPUT);
    digitalWrite(OD_4,LOW);
    pinMode(OD_5,OUTPUT);
    digitalWrite(OD_5,LOW);
    pinMode(OD_6,OUTPUT);
    digitalWrite(OD_6,LOW);
    pinMode(RELAY2,OUTPUT);
    digitalWrite(RELAY2,LOW);
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    pinMode(USB3VSNS, INPUT_ANALOG);
    pinMode(TMP1, INPUT_ANALOG);
    pinMode(TMP2, INPUT_ANALOG);
    pinMode(AUXADC1, INPUT_ANALOG);
    pinMode(AUXADC2, INPUT_ANALOG);
    pinMode(V12V, INPUT_ANALOG);
    pinMode(AIREF, INPUT_ANALOG);
    adciref = analogRead(AIREF); //Iref voltage
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
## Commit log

2020-04-05 Fixed ms printing
    Added level 0 notification in CLI when delay expires
2020-04-05 Fixed notification printing
    Fixed notification printing, cleaned up prompt printing after usage
2020-04-08 Added relay
2020-05-21 Changes for HW1.0
    Supports 6x OD outputs now, with generic parser (variables passed to it)
    Supports 7x RF switch outputs now, r1-r7 trigger command
    Supports 2nd relay now (USB2.0/3.0 power control), "m1/m2" command used
    Displays USB current/voltage when "s" status command used, displays 12V voltage also
    Added calibration/scaling based on voltage reference ADC measurement, EEPROM address 1 (2400-2600mV setting for real VREF voltage)
    Fixed printing of relay delay setting (1-1000ms) at startup

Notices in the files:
stm32_usbrelay.ino:
licensed under GNU GPL
parts and their libraries:
SparkFun: Licensing: CC v3.0 Share-Alike You are welcome to use this library for commercial purposes.
